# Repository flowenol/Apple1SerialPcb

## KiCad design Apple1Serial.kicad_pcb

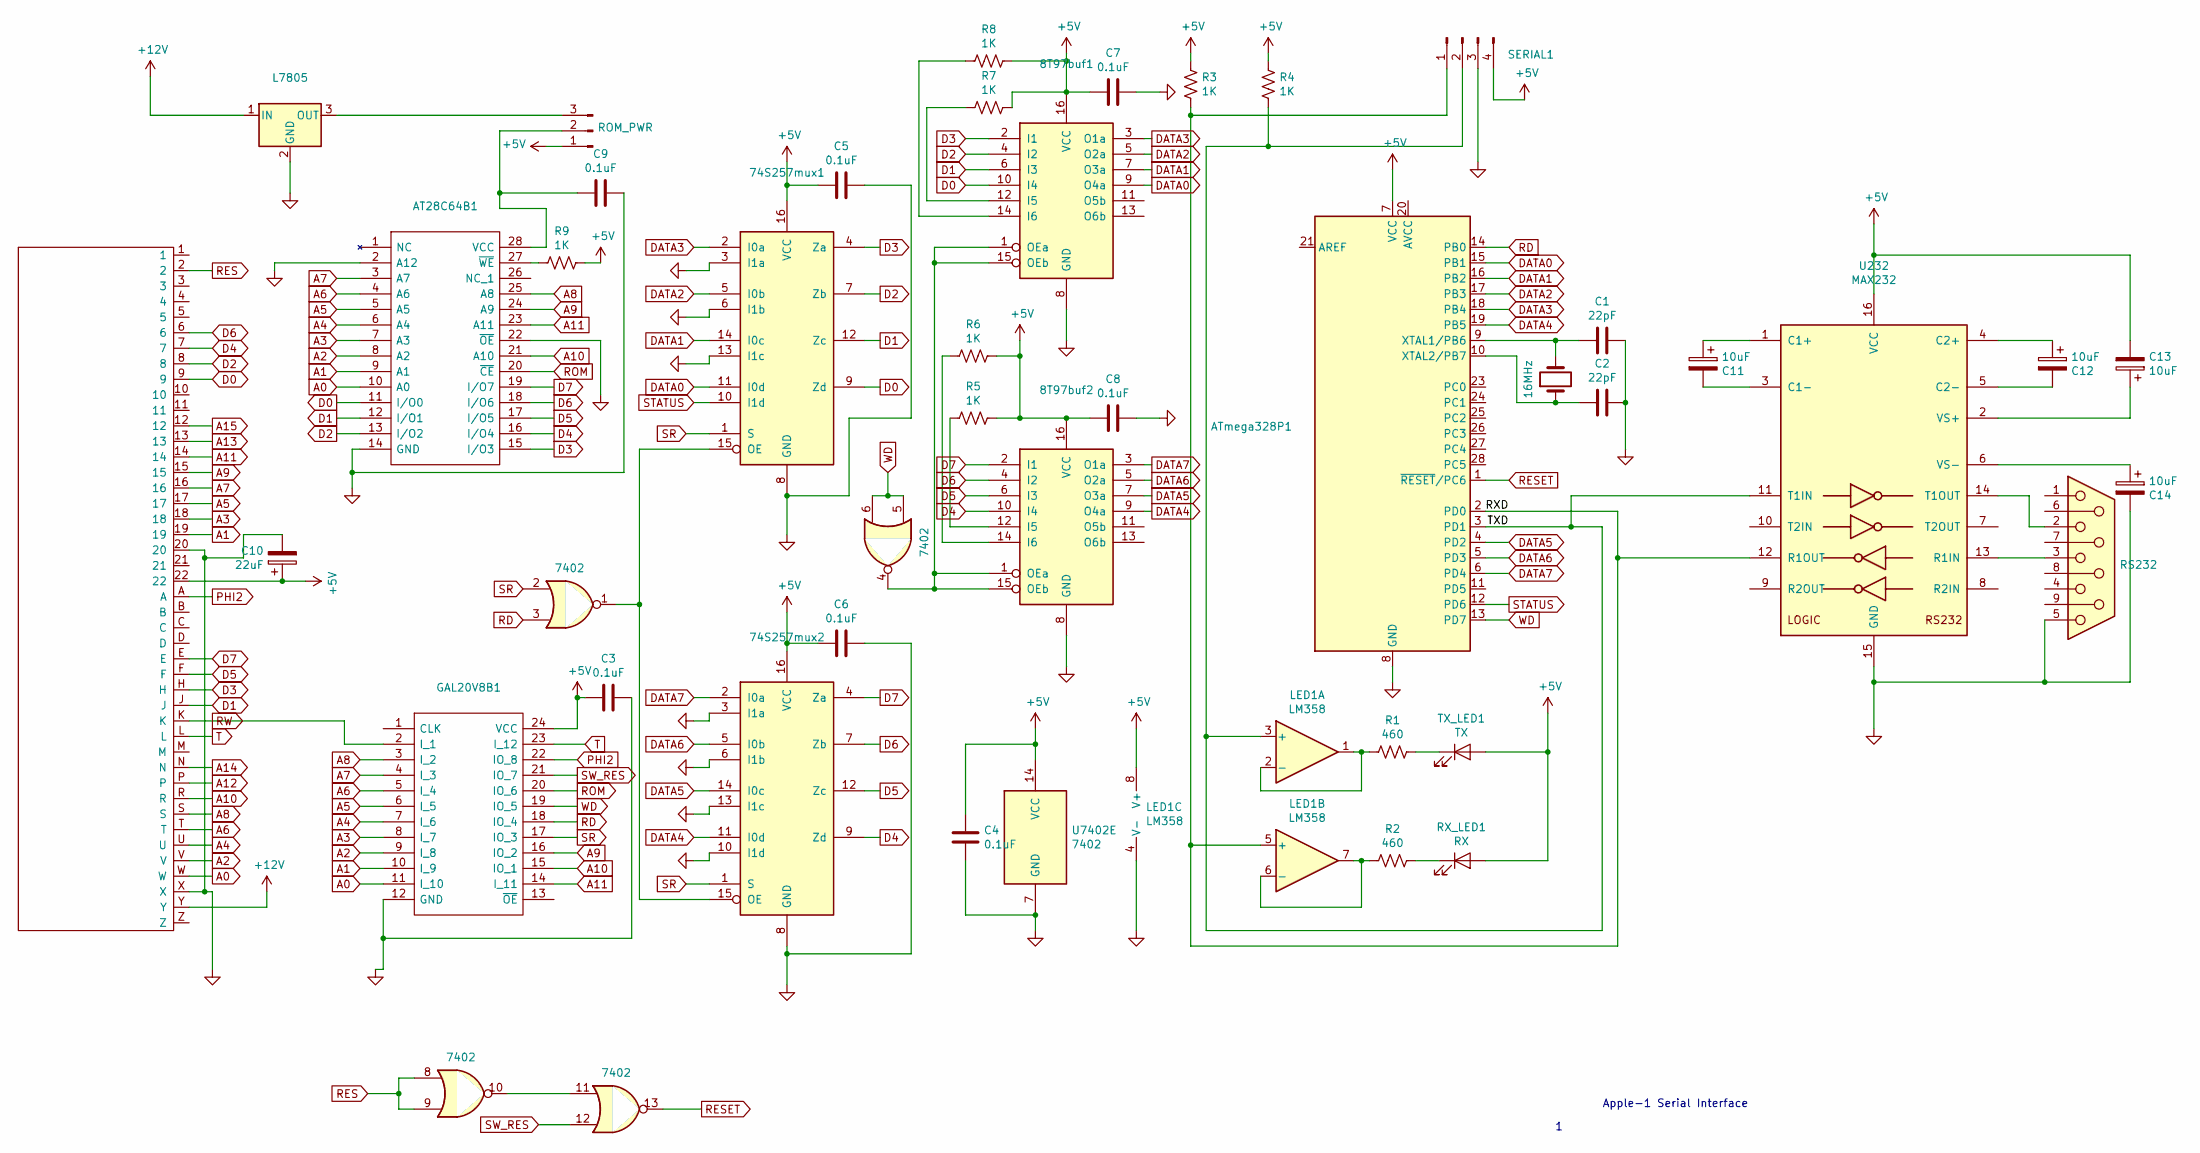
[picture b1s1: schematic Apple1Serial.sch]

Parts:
8T97buf1, 8T97buf2: 8T97; DIP-16_W7.62mm_LongPads
74S257mux1, 74S257mux2: 74S257; DIP-16_W7.62mm_LongPads
AT28C64B1: 28C64; DIP-28_W15.24mm_LongPads; Mouser Part Number 556-AT28C64B15PU
ATmega328P1: ATmega328P; DIP-28_W7.62mm_LongPads
C1, C2: 22pF; C_Disc_D5.0mm_W2.5mm_P2.50mm
C3, C4, C5, C6, C7, C8, C9: 0.1uF; C_Disc_D5.0mm_W2.5mm_P2.50mm
C10: 22uF; CP_Radial_D4.0mm_P2.00mm
C11, C12, C13, C14: 10uF; CP_Radial_D4.0mm_P2.00mm
GAL20V8B1: GAL20V8; DIP-24_W7.62mm_LongPads; Manufacturer_Part_Number GAL20V8B-15LP
L7805: L7805; TO-220-3_Horizontal_TabDown
LED1: LM358; DIP-8_W7.62mm_LongPads
R1, R2: 460; R_Axial_DIN0207_L6.3mm_D2.5mm_P7.62mm_Horizontal
R3, R4, R5, R6, R7, R8, R9: 1K; R_Axial_DIN0207_L6.3mm_D2.5mm_P7.62mm_Horizontal
ROM_PWR1: ROM_PWR; PinHeader_1x03_P2.54mm_Vertical
RS232: DB9_Female_MountingHoles; DSUB-9_Female_Horizontal_P2.77x2.84mm_EdgePinOffset4.94mm_H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
RX_LED1: RX; LED_D3.0mm
SERIAL1: SERIAL1; PinHeader_1x04_P2.54mm_Vertical
TX_LED1: TX; LED_D3.0mm
U232: MAX232; DIP-16_W7.62mm_LongPads
U7402: 7402; DIP-14_W7.62mm_LongPads
XTAL1: 16MHz; Crystal_HC49-U_Vertical
edge1: 44pin_edge; 44pin1

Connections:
+5V: 8T97buf1.16 (VCC), 8T97buf2.16 (VCC), 74S257mux1.16 (VCC), 74S257mux2.16 (VCC), ATmega328P1.7 (VCC), C3.1, C4.1, C5.1, C6.1, C7.1, C8.1, C10.1, C13.2, GAL20V8B1.24 (VCC), LED1.8 (V+), R3.1, R4.1, R5.2, R6.2, R7.2, R8.2, R9.2, ROM_PWR1.1, RX_LED1.2 (A), SERIAL1.4, TX_LED1.2 (A), U232.16 (VCC), U7402.14 (VCC), edge1.22; also elsewhere on the board
+12V: L7805.1 (IN), edge1.Y
/RXD: ATmega328P1.2 (PD0), LED1.5 (+), R3.2, SERIAL1.1, U232.12 (R1OUT); also elsewhere on the board
/TXD: ATmega328P1.3 (PD1), LED1.3 (+), R4.2, SERIAL1.2, U232.11 (T1IN); also elsewhere on the board
A0: AT28C64B1.10 (A0), GAL20V8B1.11 (I_10), edge1.W
A1: AT28C64B1.9 (A1), GAL20V8B1.10 (I_9), edge1.19
A2: AT28C64B1.8 (A2), GAL20V8B1.9 (I_8), edge1.V
A3: AT28C64B1.7 (A3), GAL20V8B1.8 (I_7), edge1.18
A4: AT28C64B1.6 (A4), GAL20V8B1.7 (I_6), edge1.U
A5: AT28C64B1.5 (A5), GAL20V8B1.6 (I_5), edge1.17
A6: AT28C64B1.4 (A6), GAL20V8B1.5 (I_4), edge1.T
A7: AT28C64B1.3 (A7), GAL20V8B1.4 (I_3), edge1.16
A8: AT28C64B1.25 (A8), GAL20V8B1.3 (I_2), edge1.S
A9: AT28C64B1.24 (A9), GAL20V8B1.16 (IO_2), edge1.15
A10: AT28C64B1.21 (A10), GAL20V8B1.15 (IO_1), edge1.R
A11: AT28C64B1.23 (A11), GAL20V8B1.14 (I_11), edge1.14
A12: edge1.P
A13: edge1.13
A14: edge1.N
A15: edge1.12
D0: 8T97buf1.10 (I4), 74S257mux1.9 (Zd), AT28C64B1.11 (I/O0), edge1.9
D1: 8T97buf1.6 (I3), 74S257mux1.12 (Zc), AT28C64B1.12 (I/O1), edge1.J
D2: 8T97buf1.4 (I2), 74S257mux1.7 (Zb), AT28C64B1.13 (I/O2), edge1.8
D3: 8T97buf1.2 (I1), 74S257mux1.4 (Za), AT28C64B1.15 (I/O3), edge1.H
D4: 8T97buf2.10 (I4), 74S257mux2.9 (Zd), AT28C64B1.16 (I/O4), edge1.7
D5: 8T97buf2.6 (I3), 74S257mux2.12 (Zc), AT28C64B1.17 (I/O5), edge1.F
D6: 8T97buf2.4 (I2), 74S257mux2.7 (Zb), AT28C64B1.18 (I/O6), edge1.6
D7: 8T97buf2.2 (I1), 74S257mux2.4 (Za), AT28C64B1.19 (I/O7), edge1.E
DATA0: 8T97buf1.9 (O4a), 74S257mux1.11 (I0d), ATmega328P1.15 (PB1)
DATA1: 8T97buf1.7 (O3a), 74S257mux1.14 (I0c), ATmega328P1.16 (PB2)
DATA2: 8T97buf1.5 (O2a), 74S257mux1.5 (I0b), ATmega328P1.17 (PB3)
DATA3: 8T97buf1.3 (O1a), 74S257mux1.2 (I0a), ATmega328P1.18 (PB4)
DATA4: 8T97buf2.9 (O4a), 74S257mux2.11 (I0d), ATmega328P1.19 (PB5)
DATA5: 8T97buf2.7 (O3a), 74S257mux2.14 (I0c), ATmega328P1.4 (PD2)
DATA6: 8T97buf2.5 (O2a), 74S257mux2.5 (I0b), ATmega328P1.5 (PD3)
DATA7: 8T97buf2.3 (O1a), 74S257mux2.2 (I0a), ATmega328P1.6 (PD4)
GND: 8T97buf1.8 (GND), 8T97buf2.8 (GND), 74S257mux1.3 (I1a), 74S257mux1.6 (I1b), 74S257mux1.8 (GND), 74S257mux1.13 (I1c), 74S257mux2.3 (I1a), 74S257mux2.6 (I1b), 74S257mux2.8 (GND), 74S257mux2.10 (I1d), 74S257mux2.13 (I1c), AT28C64B1.2 (A12), AT28C64B1.14 (GND), AT28C64B1.22 (~OE), ATmega328P1.8 (GND), ATmega328P1.22 (GND), C1.2, C2.2, C3.2, C4.2, C5.2, C6.2, C7.2, C8.2, C9.2, C10.2, C14.2, GAL20V8B1.12 (GND), L7805.2 (GND), LED1.4 (V-), RS232.5, SERIAL1.3, U232.15 (GND), U7402.7 (GND), edge1.20, edge1.X; also elsewhere on the board
unnamed: 8T97buf1.1 (OEa), 8T97buf1.15 (OEb), 8T97buf2.1 (OEa), 8T97buf2.15 (OEb), U7402.4
unnamed: 8T97buf1.12 (I5), R7.1
unnamed: 8T97buf1.14 (I6), R8.1
unnamed: 8T97buf2.12 (I5), R5.1
unnamed: 8T97buf2.14 (I6), R6.1
unnamed: 74S257mux1.15 (OE), 74S257mux2.15 (OE), U7402.1
unnamed: AT28C64B1.27 (~WE), R9.1
unnamed: AT28C64B1.28 (VCC), C9.1, ROM_PWR1.2
unnamed: ATmega328P1.9 (XTAL1/PB6), C1.1, XTAL1.2
unnamed: ATmega328P1.10 (XTAL2/PB7), C2.1, XTAL1.1
unnamed 62: C11.1, U232.1 (C1+); also elsewhere on the board
unnamed 63: C11.2, U232.3 (C1-); also elsewhere on the board
unnamed 64: C12.1, U232.4 (C2+); also elsewhere on the board
unnamed 65: C12.2, U232.5 (C2-); also elsewhere on the board
unnamed 66: C13.1, U232.2 (VS+); also elsewhere on the board
unnamed 67: C14.1, U232.6 (VS-); also elsewhere on the board
unnamed: L7805.3 (OUT), ROM_PWR1.3
unnamed: LED1.1, LED1.2 (-), R1.1
unnamed: LED1.6 (-), LED1.7, R2.1
unnamed: R1.2, TX_LED1.1 (K)
unnamed: R2.2, RX_LED1.1 (K)
unnamed 76: RS232.2, U232.14 (T1OUT); also elsewhere on the board
unnamed 77: RS232.3, U232.13 (R1IN); also elsewhere on the board
unnamed: U7402.10, U7402.11
PHI2: GAL20V8B1.22 (IO_8), edge1.A
RD: ATmega328P1.14 (PB0), GAL20V8B1.18 (IO_4), U7402.3
RES: U7402.8, U7402.9, edge1.2
RESET: ATmega328P1.1 (~RESET~/PC6), U7402.13
ROM: AT28C64B1.20 (~CE), GAL20V8B1.20 (IO_6)
RW: GAL20V8B1.2 (I_1), edge1.K
SR: 74S257mux1.1 (S), 74S257mux2.1 (S), GAL20V8B1.17 (IO_3), U7402.2
STATUS: 74S257mux1.10 (I1d), ATmega328P1.12 (PD6)
SW_RES: GAL20V8B1.21 (IO_7), U7402.12
T: GAL20V8B1.23 (I_12), edge1.L
WD: ATmega328P1.13 (PD7), GAL20V8B1.19 (IO_5), U7402.5, U7402.6

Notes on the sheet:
Apple-1 Serial Interface

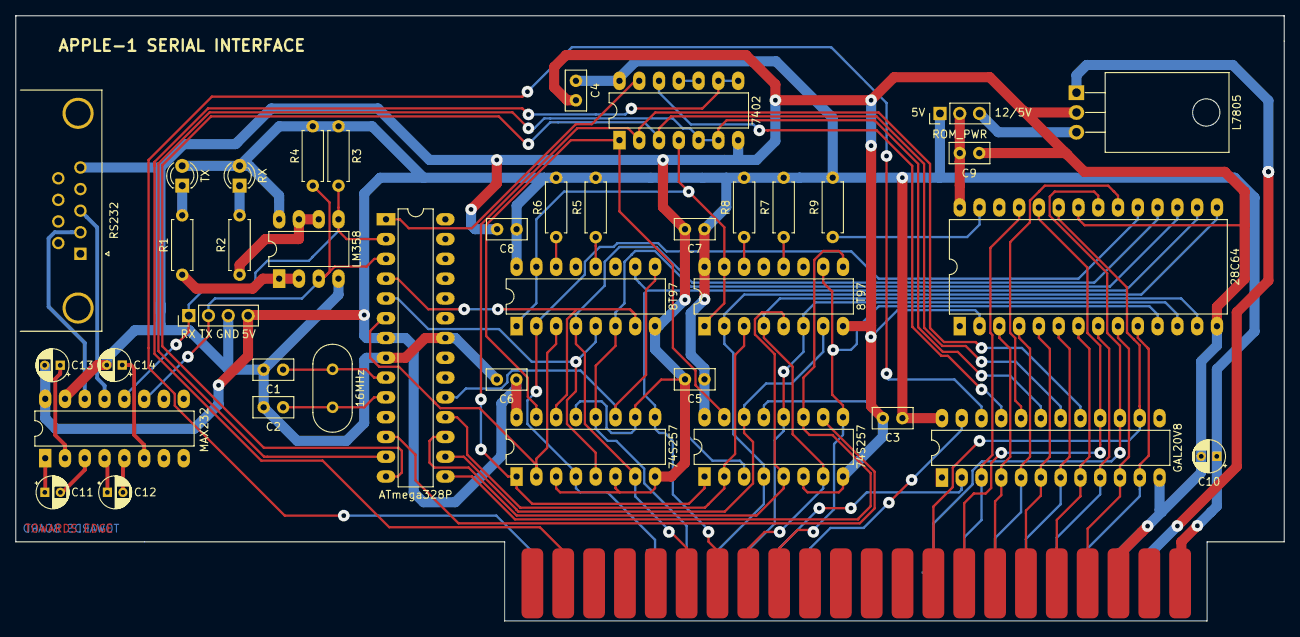
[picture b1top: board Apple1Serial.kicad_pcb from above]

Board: 2 copper layers, 162.8 x 77.7 mm, 41 parts (0 on the bottom side), 68 nets.

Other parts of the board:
MAX232: MAX232; DIP-16_W7.62mm_LongPads

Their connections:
+5V: MAX232.16; also elsewhere on the board
/RXD: MAX232.12; also elsewhere on the board
/TXD: MAX232.11; also elsewhere on the board
GND: MAX232.15; also elsewhere on the board
unnamed 62: MAX232.1; also elsewhere on the board
unnamed 63: MAX232.3; also elsewhere on the board
unnamed 64: MAX232.4; also elsewhere on the board
unnamed 65: MAX232.5; also elsewhere on the board
unnamed 66: MAX232.2; also elsewhere on the board
unnamed 67: MAX232.6; also elsewhere on the board
unnamed 76: MAX232.14; also elsewhere on the board
unnamed 77: MAX232.13; also elsewhere on the board

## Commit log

2021-03-03 Added .gitignore
2021-03-05 Fixed element values on schematics
2023-01-10 replaced R with T
2023-05-25 Added DB9 rs232 connector
